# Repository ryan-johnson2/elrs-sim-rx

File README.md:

# ELRS Sim RX

An ExpressLRS receiver to USB gamepad adapter for FPV simulators, built on an RP2040. Plug it
in, bind your radio to it, and the radio shows up as a game controller in Liftoff,
Velocidrone, Uncrashed, Tryp and anything else that reads a standard HID gamepad. You fly the
sim over the same radio link, packet rate and radio setup you fly for real.

## How this was made

All of the code and all of the hardware design in this repository were produced with AI:
Anthropic's Claude, working through Claude Code. That covers the firmware, the configuration
page, the tests, the schematics and PCB layouts, the printed cases and the documentation.

A person directed the work, built the hardware, and tested it on the bench and in simulators.
Read it with that in mind: parts of it have had real use, parts have only passed automated
checks, and the status table below says which.

## Status

| Part | State |
|---|---|
| Firmware core: gamepad, CRSF, failsafe, receiver power, bind, model match, passthrough | In daily use on the perfboard prototype |
| Newer firmware features: profiles, the lite build, the onboard status LED, bootloader without the drive | Pass the automated tests; little or no time on hardware yet |
| Configuration page | In use; the four-tab layout, profiles and one-click update are tested against a simulated device only |
| Prototype hardware (breadboard, then perfboard) | Built and working |
| Carrier PCB v0.2 | Ordered, not yet received or tested |
| Integrated PCB with the RP2040 on board | Draft: placed, not routed |
| Printed cases | Designed and checked for overlaps in CAD; not confirmed on a printer |
| Hosting on GitHub Pages, release and development builds | CI builds, tests and publishes the development firmware; no release tagged yet |

## What it does

- **Gamepad:** 8 axes at 16-bit resolution, with the full 11-bit CRSF channel range kept, and
  36 buttons derived from switch channels. A report goes out on every CRSF frame, up to the
  1 kHz USB polling rate.
- **Failsafe:** sticks centred and throttle low within 100 ms of losing the link.
- **Receiver power:** a front-panel button switches the receiver off and on, so the dongle
  can stay plugged in while you fly something else. A long press puts the receiver into bind
  mode.
- **Status light:** the button's LED ring mirrors the receiver's own status LED patterns.
- **Profiles:** 16 named channel-to-axis and channel-to-button mappings stored on the dongle.
- **Receiver updates:** Betaflight-compatible passthrough, so the ExpressLRS Web Flasher or
  Configurator can update the receiver and set its bind phrase through the dongle.
- **Receiver settings:** model match, and on ExpressLRS 4.0 or newer the receiver's own
  settings, from the configuration page.
- **No drivers:** a standard USB gamepad plus a serial port on Windows, Linux and macOS.

## Hardware

There are three generations of the same circuit: a hand-built prototype, a carrier PCB that
takes an RP2040-Zero module, and a draft board with the RP2040 itself fitted.
**[docs/HARDWARE.md](docs/HARDWARE.md)** is the index, with the state of each.

| | Page |
|---|---|
| Parts list, pin plan, costs | [docs/HBOM.md](docs/HBOM.md) |
| Breadboard build, step by step | [web/guides/breadboard-build.html](web/guides/breadboard-build.html) |
| Perfboard layout, hole by hole | [web/guides/perfboard-layout.html](web/guides/perfboard-layout.html) |
| Carrier PCB v0.2 | [hardware/carrier/](hardware/carrier/README.md) |
| Integrated PCB draft | [hardware/board/](hardware/board/README.md) |
| Cases | [prototype](hardware/case-proto/README.md), [carrier](hardware/case-carrier/README.md) |
| Bring-up checklist | [docs/BRINGUP.md](docs/BRINGUP.md) |
| What the status light means | [docs/LED-BEHAVIOUR.md](docs/LED-BEHAVIOUR.md) |

The simplest build needs no PCB at all: an RP2040-Zero and a receiver joined by four wires
(5V, GND, GP0 to the receiver's RX pad, GP1 to its TX pad), running the lite firmware.

## Firmware

Pico SDK and TinyUSB, in C. One build tree produces two files:

| File | For |
|---|---|
| `elrs_sim_rx.uf2` | Any board with the power switch, button and LED ring |
| `elrs_sim_rx_lite.uf2` | A module wired straight to a receiver. The receiver is on whenever USB is |

To flash: hold BOOT while plugging the board in, then copy the file onto the `RPI-RP2` drive
that appears. After that, updates can be done from the configuration page.

Details, the console commands and the flash layout are in
[docs/FIRMWARE.md](docs/FIRMWARE.md).

## Configuring

`web/index.html` is a single static page that talks to the dongle over Web Serial, so it
needs Chrome or Edge on a desktop. Click Connect and pick the device. It has five tabs:

- **Controller** (the page it opens on): profiles and saving, live channels, the axis and
  button mapping, link status, receiver power, bind, model match and the receiver's own settings.
- **Firmware:** update the dongle itself.
- **RX flashing:** the short steps for updating the receiver's ExpressLRS firmware through
  the dongle, with a link to the ExpressLRS Web Flasher.
- **Console:** the raw console and counters.
- **Docs:** the user documentation.

Changes apply at once; **Save to device** writes them to the active profile.

The same serial port answers a plain terminal at any baud rate: type `help`.

See [docs/WEBUI.md](docs/WEBUI.md) for how the page works and is hosted, and
[docs/WINDOWS.md](docs/WINDOWS.md) for the one optional Windows driver step.

## Building

Everything runs in Docker; nothing else needs installing on the host.

```
tools/build.sh        # firmware -> firmware/build/elrs_sim_rx.uf2 and elrs_sim_rx_lite.uf2
tools/test.sh         # host unit tests for the hardware-independent core
tools/test-web.sh     # configuration page and bootloader tests (Playwright image)
tools/serve.sh        # serve the page and the latest firmware over HTTPS on the LAN
tools/flash.sh        # flash a board plugged into this machine (Linux)
tools/shell.sh        # shell inside the build container
```

`tools/serve.sh` is the easy way to work when the build machine and the PC with the dongle
are different computers: open the address it prints in Chrome or Edge on that PC.

Hardware builds (PCB generation and checks, order files, case exports) are listed in
[docs/HARDWARE.md](docs/HARDWARE.md).

## Versions

The firmware and the configuration page are released together under one version: a `vX.Y.Z`
tag on `main`. The page is published alongside the firmware it flashes, so the two always
match. Builds that are not on a release tag name themselves after the next patch version, the
number of commits since the last release and the commit, for example `0.1.1-dev.4+3664729`;
`tools/version.sh` works this out and `version` on the console reports it.

Each board has its own revision, printed on its silkscreen, and is not part of the release
number. The commit a board was ordered from is tagged `<board>-v<revision>`, for example
`carrier-v0.2`. Release notes say which boards a firmware release supports.

## Layout

| Path | Contents |
|------|----------|
| `firmware/` | Firmware. `core/` is hardware independent and unit tested; `src/` is the RP2040 side |
| `tests/` | Host unit tests, and browser tests for the configuration page |
| `web/` | The configuration page, the bootloader flasher, and the build guides |
| `hardware/` | KiCad projects for the two PCBs, their generator scripts, and the OpenSCAD cases |
| `docs/` | Hardware index, parts list, bring-up checklist, firmware and page notes |
| `tools/` | Build container and helper scripts |
| `.github/workflows/` | CI: build, test, and publishing of the page and firmware |

Only sources are committed. Firmware binaries, PCB renders and order files, case STLs and the
wiring PDF are generated by the commands above.

## License

Firmware and documentation are licensed under the Apache License 2.0. See `LICENSE`.

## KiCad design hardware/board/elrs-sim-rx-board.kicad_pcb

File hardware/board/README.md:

# Integrated board (draft v0.1, placed, not routed)

KiCad 9 project for the next board after the carrier: the RP2040 itself is on the board, so
there is no module to solder. The fab fits everything except the receiver and the button leads.

| | |
|---|---|
| Board | 22 x 39.1 mm, 2 layers, same outline, receiver cut-out, button pads and M2 hole as carrier v0.2 |
| MCU | RP2040, W25Q16 flash, 12 MHz crystal, XC6206 3.3 V regulator, USB-C socket |
| Kept from the module | BOOT button. No RESET button; the RUN pin has a pull-up |
| Status light | One plain LED on GP25. The firmware drives GP25 and the RP2040-Zero's RGB LED on GP16 with the same pattern, so one build serves both boards |
| Receiver | Happymodel EP2 soldered by its castellated edge over the cut-out, as on the carrier |
| Button | Four pads: LED+, LED-, BTN, BTN. Leave the button off for the no-button version |
| Circuit | Otherwise the carrier's: TPS22918 load switch on GP2, 2N7002 LED driver on GP4, button on GP3, CRSF on GP0 / GP1 |
| Debug | SWCLK and SWDIO test pads |

## State

- Schematic: complete, ERC clean. It is drawn label-style (every pin carries a net name, no
  wires) because it is generated from a parts table in `gen/gen_sch.py`.
- Placement: all 48 footprints placed, no courtyard overlaps.
- Routing: none yet. `gen/route.sh` runs the Freerouting autorouter on the exported
  `out/elrs-sim-rx-board.dsn` and imports the result; it has not been run.
- Part numbers: only the RP2040, USB-C socket, regulator, load switch and LED driver have LCSC
  numbers. The flash, crystal, button, LED and all the 0402 passives still need choosing, and
  the crystal's load capacitors (drawn as 15 pF) depend on the crystal picked.

## To do before this can be ordered

1. Route it, then review the result by hand: USB pair, crystal, decoupling and the ground pour.
2. Choose and confirm every part number; pick the crystal and set C17 / C18 to match.
3. Decide on USB ESD protection (none drawn).
4. Check the EP2 pad pitch (shared with the carrier; `RX_PITCH` in `gen/gen_pcb.py`).
5. Firmware: confirm the build boots with this flash and crystal. The pin map is unchanged.

## Regenerate and check

```
tools/kicad.sh hardware/board/gen/build.sh          # schematic, placement, ERC, DRC, renders
hardware/board/gen/route.sh                          # autoroute and import (run on the host)
```

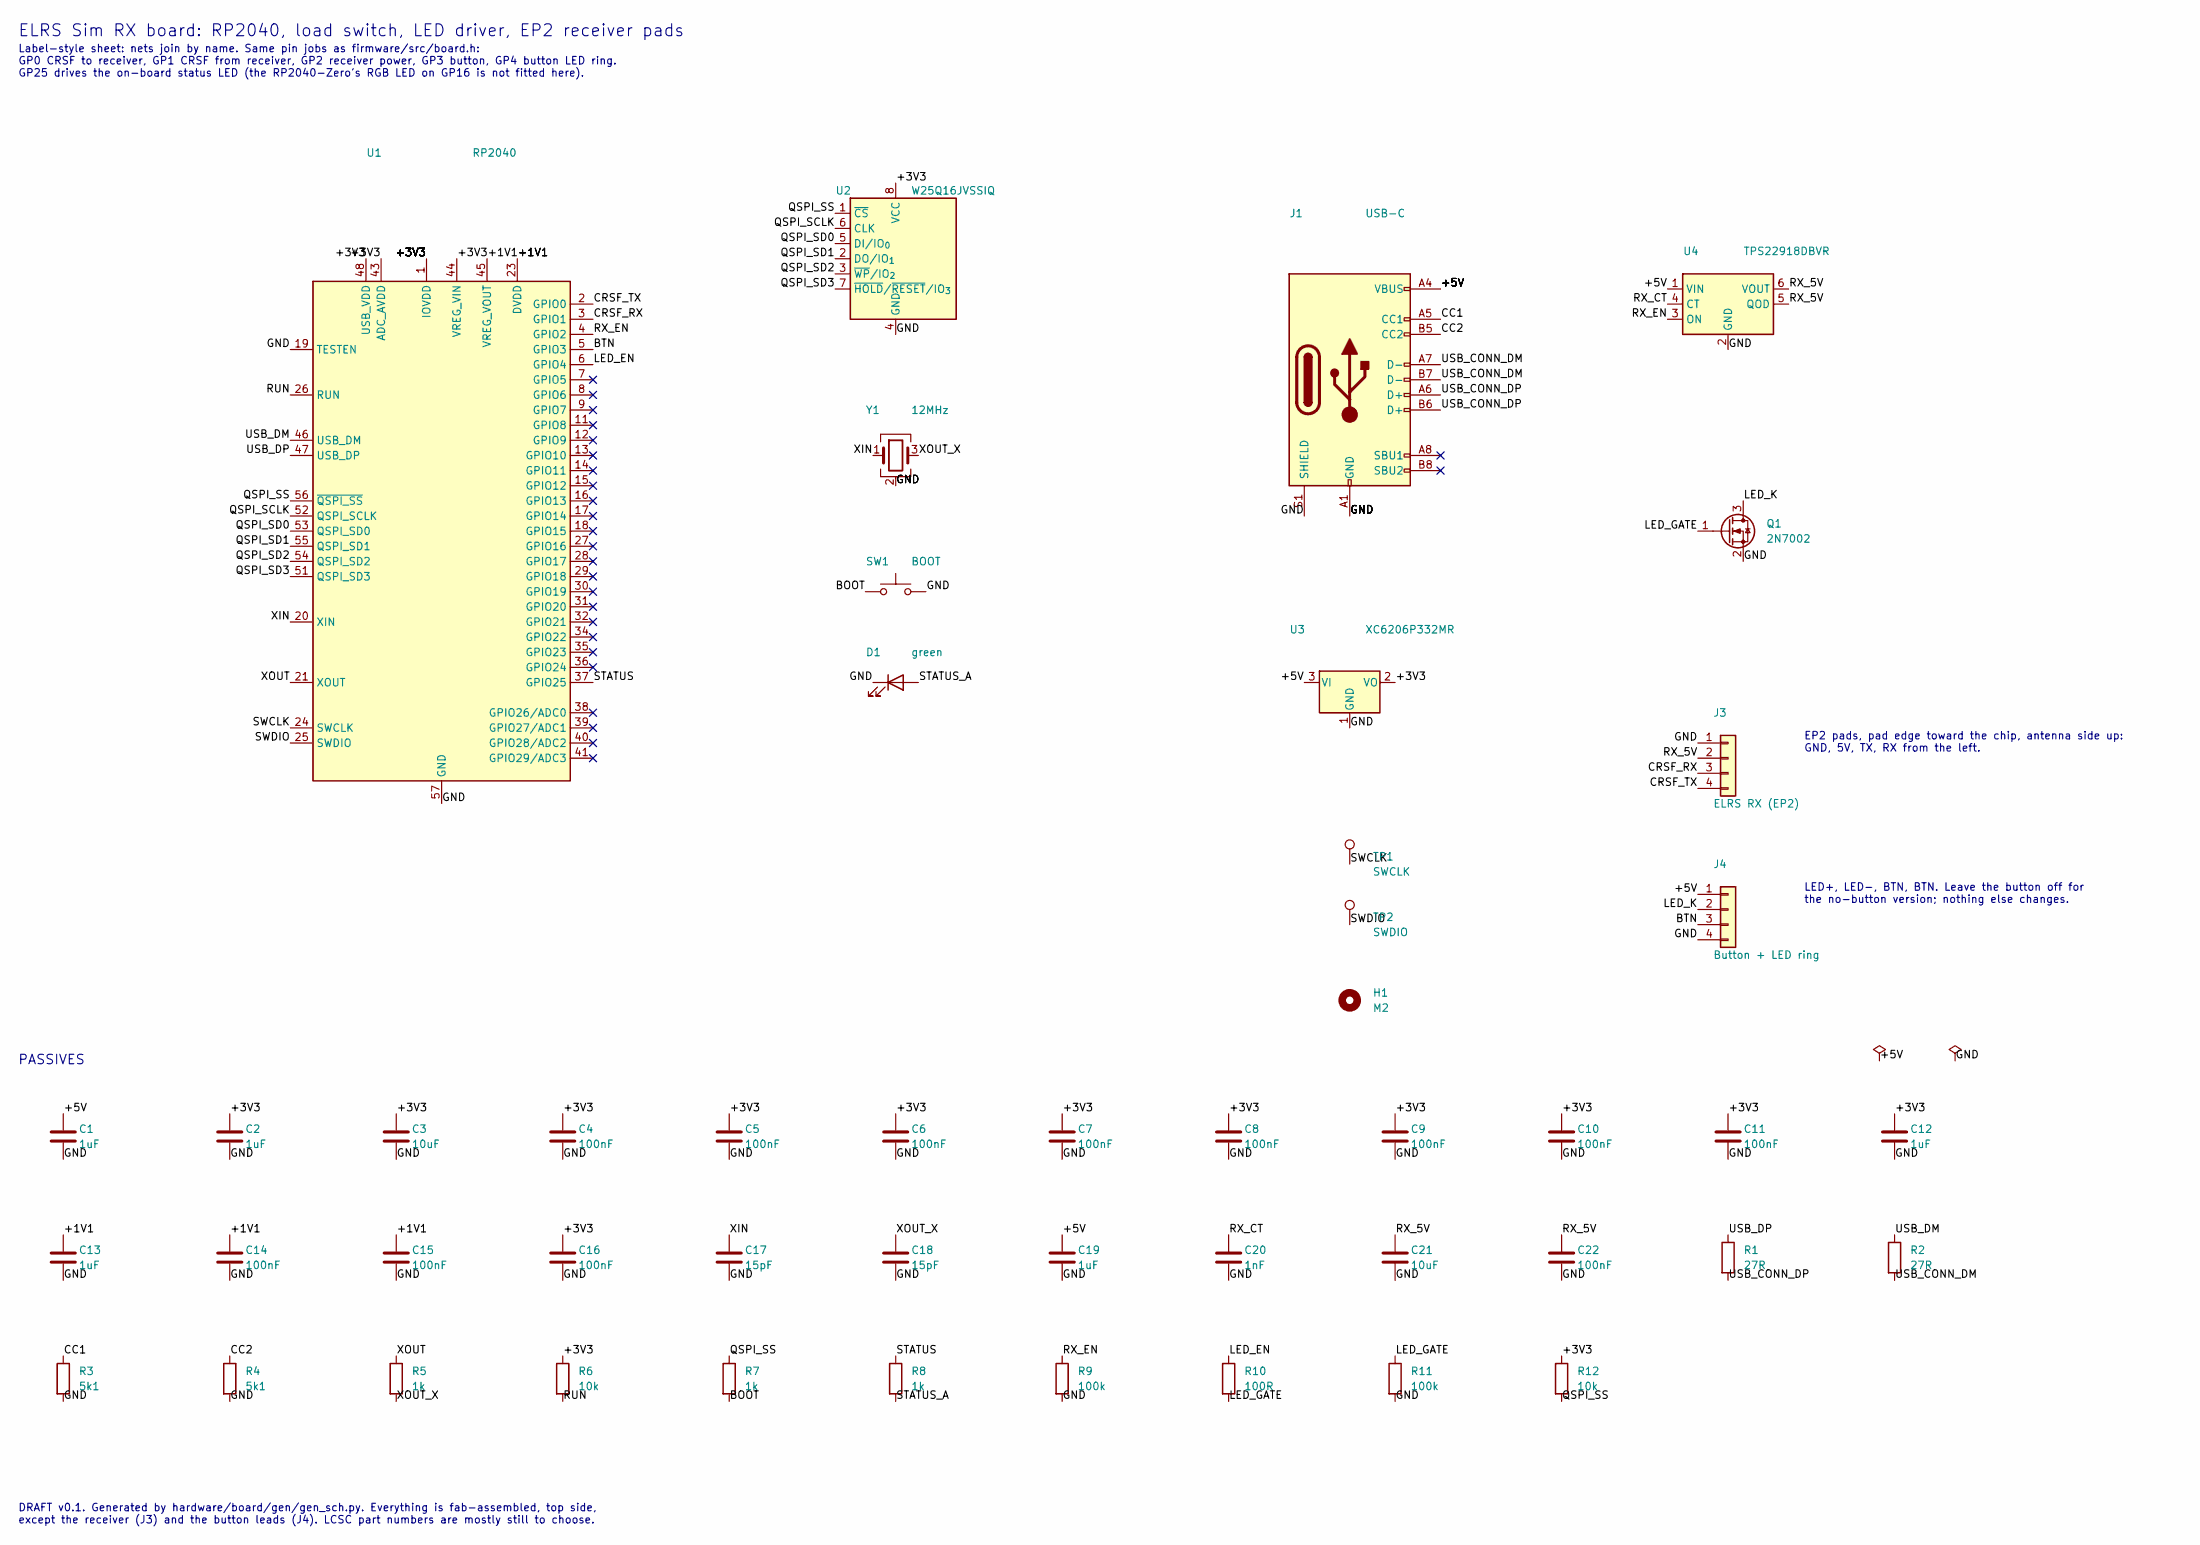
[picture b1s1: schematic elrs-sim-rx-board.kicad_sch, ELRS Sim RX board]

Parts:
C1, C2, C12, C13, C19: 1uF; C_0402_1005Metric
C3: 10uF; C_0603_1608Metric
C4, C5, C6, C7, C8, C9, C10, C11, C14, C15, C16, C22: 100nF; C_0402_1005Metric
C17, C18: 15pF; C_0402_1005Metric
C20: 1nF; C_0402_1005Metric
C21: 10uF; C_0805_2012Metric
D1: green; LED_0603_1608Metric
H1: M2; MountingHole_2.2mm_M2
J1: USB-C; USB_C_Receptacle_HRO_TYPE-C-31-M-12; MPN TYPE-C-31-M-12; LCSC C165948
J3: ELRS RX (EP2); ELRS_RX_4pad_castellated
J4: Button + LED ring; PinHeader_1x04_P2.54mm_Vertical
Q1: 2N7002; SOT-23; LCSC C8545
R1, R2: 27R; R_0402_1005Metric
R3, R4: 5k1; R_0402_1005Metric
R5, R7, R8: 1k; R_0402_1005Metric
R6, R12: 10k; R_0402_1005Metric
R9, R11: 100k; R_0402_1005Metric
R10: 100R; R_0402_1005Metric
SW1: BOOT; SW_SPST_B3U-1000P
TP1: SWCLK; TestPoint_Pad_D1.0mm
TP2: SWDIO; TestPoint_Pad_D1.0mm
U1: RP2040; QFN-56-1EP_7x7mm_P0.4mm_EP3.2x3.2mm; MPN RP2040; LCSC C2040
U2: W25Q16JVSSIQ; SOIC-8_5.3x5.3mm_P1.27mm; MPN W25Q16JVSSIQ
U3: XC6206P332MR; SOT-23; MPN XC6206P332MR; LCSC C5446
U4: TPS22918DBVR; SOT-23-6; MPN TPS22918DBVR; LCSC C131941
Y1: 12MHz; Crystal_SMD_3225-4Pin_3.2x2.5mm

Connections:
/+1V1: C13.1, C14.1, C15.1, U1.23 (DVDD), U1.45 (VREG_VOUT), U1.50 (DVDD)
/+3V3: C2.1, C3.1, C4.1, C5.1, C6.1, C7.1, C8.1, C9.1, C10.1, C11.1, C12.1, C16.1, R6.1, R12.1, U1.1 (IOVDD), U1.10 (IOVDD), U1.22 (IOVDD), U1.33 (IOVDD), U1.42 (IOVDD), U1.43 (ADC_AVDD), U1.44 (VREG_VIN), U1.48 (USB_VDD), U1.49 (IOVDD), U2.8 (VCC), U3.2 (VO)
/+5V: C1.1, C19.1, J1.A4 (VBUS), J1.A9 (VBUS), J1.B4 (VBUS), J1.B9 (VBUS), J4.1, U3.3 (VI), U4.1 (VIN)
/BOOT: R7.2, SW1.1
/BTN: J4.3, U1.5 (GPIO3)
/CC1: J1.A5 (CC1), R3.1
/CC2: J1.B5 (CC2), R4.1
/CRSF_RX: J3.3, U1.3 (GPIO1)
/CRSF_TX: J3.4, U1.2 (GPIO0)
/GND: C1.2, C2.2, C3.2, C4.2, C5.2, C6.2, C7.2, C8.2, C9.2, C10.2, C11.2, C12.2, C13.2, C14.2, C15.2, C16.2, C17.2, C18.2, C19.2, C20.2, C21.2, C22.2, D1.1 (K), J1.A1 (GND), J1.A12 (GND), J1.B1 (GND), J1.B12 (GND), J1.S1 (SHIELD), J3.1, J4.4, Q1.2 (S), R3.2, R4.2, R9.2, R11.2, SW1.2, U1.19 (TESTEN), U1.57 (GND), U2.4 (GND), U3.1 (GND), U4.2 (GND), Y1.2 (G), Y1.4 (G)
/LED_EN: R10.1, U1.6 (GPIO4)
/LED_GATE: Q1.1 (G), R10.2, R11.1
/LED_K: J4.2, Q1.3 (D)
/QSPI_SCLK: U1.52 (QSPI_SCLK), U2.6 (CLK)
/QSPI_SD0: U1.53 (QSPI_SD0), U2.5 (DI/IO_{0})
/QSPI_SD1: U1.55 (QSPI_SD1), U2.2 (DO/IO_{1})
/QSPI_SD2: U1.54 (QSPI_SD2), U2.3 (~WP/IO_{2})
/QSPI_SD3: U1.51 (QSPI_SD3), U2.7 (~HOLD/~RESET/IO_{3})
/QSPI_SS: R7.1, R12.2, U1.56 (~QSPI_SS), U2.1 (~CS)
/RUN: R6.2, U1.26 (RUN)
/RX_5V: C21.1, C22.1, J3.2, U4.5 (QOD), U4.6 (VOUT)
/RX_CT: C20.1, U4.4 (CT)
/RX_EN: R9.1, U1.4 (GPIO2), U4.3 (ON)
/STATUS: R8.1, U1.37 (GPIO25)
/STATUS_A: D1.2 (A), R8.2
/SWCLK: TP1.1, U1.24 (SWCLK)
/SWDIO: TP2.1, U1.25 (SWDIO)
/USB_CONN_DM: J1.A7 (D-), J1.B7 (D-), R2.2
/USB_CONN_DP: J1.A6 (D+), J1.B6 (D+), R1.2
/USB_DM: R2.1, U1.46 (USB_DM)
/USB_DP: R1.1, U1.47 (USB_DP)
/XIN: C17.1, U1.20 (XIN), Y1.1
/XOUT: R5.1, U1.21 (XOUT)
/XOUT_X: C18.1, R5.2, Y1.3

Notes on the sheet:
ELRS Sim RX board: RP2040, load switch, LED driver, EP2 receiver pads
Label-style sheet: nets join by name. Same pin jobs as firmware/src/board.h: GP0 CRSF to receiver, GP1 CRSF from receiver, GP2 receiver power, GP3 button, GP4 button LED ring. GP25 drives the on-board status LED (the RP2040-Zero's RGB LED on GP16 is not fitted here).
EP2 pads, pad edge toward the chip, antenna side up: GND, 5V, TX, RX from the left.
LED+, LED-, BTN, BTN. Leave the button off for the no-button version; nothing else changes.
PASSIVES
DRAFT v0.1. Generated by hardware/board/gen/gen_sch.py. Everything is fab-assembled, top side, except the receiver (J3) and the button leads (J4). LCSC part numbers are mostly still to choose.

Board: 2 copper layers, 48 parts (0 on the bottom side), 34 nets, no tracks yet.

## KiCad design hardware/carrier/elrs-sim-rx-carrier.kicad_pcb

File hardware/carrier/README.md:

# Carrier board (draft v0.2)

KiCad 9 project for the Phase 2 carrier in [docs/HBOM.md](../../docs/HBOM.md). v0.2 follows the
Phase 1 breadboard and perfboard builds: the module is soldered in directly, the back-row
socket is gone, and the receiver mount was redrawn for the Happymodel EP2. Five boards were made
(JLCPCB, ordered 2026-11-14); the first was assembled and brought up on 2026-11-24.

| | |
|---|---|
| Board | 22 x 39.1 mm with the lower left corner cut away for the receiver, 2 layers, one M2 hole |
| MCU | RP2040-Zero soldered in by its own pin headers: two 1x9 rows of plated holes (J1, J2) and five unconnected holes for the back-row pins (J5), so the module drops in unmodified |
| Receiver | Happymodel EP2, antenna side up, soldered by its castellated edge onto four SMD pads (J3) and hanging over the cut-out, since it has parts on both faces |
| Button | Four pads (J4) marked by function: LED+, LED-, BTN, BTN. The switch's two leads go to the two BTN pads, either way round (one of them is ground) |
| Fab-assembled | U1, Q1, R1 to R3, C1 to C4. All top side, all under the module |
| Hand-soldered | The module, the receiver, the button leads |

## Circuit

Electrically the same as the Phase 1 breadboard build with the planned Phase 2 swaps:

- TPS22918 load switch replaces AO3401A + 2N7000 + 10 k. GP2 drives ON directly; R1 (100 k)
  holds the receiver off until firmware takes over. QOD is tied to VOUT so the rail collapses
  quickly, which the power-cycle bind sequence needs.
- 2N7002 replaces the 2N7000 LED ring driver, same 100 R gate resistor and 100 k pull-down.
- Pin map is unchanged from `firmware/src/board.h`. No firmware changes are needed.

## Checks

1. **EP2 pad order: confirmed on board 1** (2026-11-24: receiver powers, CRSF frames arrive on
   GP1, passthrough flashing works). GND, 5V, TX, RX from the left with the pad edge toward the
   module and the antenna side up; ground is the end pad on the antenna's side. The EP2 itself
   has no pad labels.
2. **EP2 pad pitch and underside: checked.** A photo of a real EP2 on a steel rule
   (2026-11-14) shows the outer pads 7.6 mm apart, so 2.54 mm pitch, centred on the edge, and
   nothing taller than a bare pad within 2.2 mm of the pad edge on the ESP side.
3. **RP2040-Zero pin grid.** Two rows of nine, 15.24 mm apart, pin 1 (5V left, GP0 right) at
   the USB end, and the five back-row holes in line with the last pin of each side row.
   Confirmed on board 1: an unmodified module drops in.
4. **Height under the module.** The SMD parts sit under the soldered-in module, which stands
   about 2.5 mm off the board on its header spacers. The tallest part is the 0805 capacitor.
5. **LCSC part numbers** in the schematic `LCSC` field were filled in from memory. Confirm
   each one, and add one for U1, before generating a JLCPCB BOM.
6. **Mounting.** One M2 hole on the arm beside the receiver. The receiver is held only by
   its four solder joints, so the case should support its free end.

## Files

- `elrs-sim-rx-carrier.kicad_pro`, `.kicad_sch`, `.kicad_pcb`: the project.
- `carrier.kicad_sym`, `sym-lib-table`: project symbol library (TPS22918).
- `carrier.pretty/`, `fp-lib-table`: project footprint library (receiver landing).
- `gen/`: the scripts that produced the draft. Placement and routing are written out by hand
  in `gen_pcb.py`. Regenerating overwrites the schematic and board, so stop using the scripts
  once you start editing in KiCad.

## Regenerate and check

KiCad runs in the official container; nothing is installed on the host.

```
tools/kicad.sh hardware/carrier/gen/build.sh          # regenerate, ERC, DRC, previews
tools/kicad.sh hardware/carrier/gen/build.sh check    # ERC, DRC, previews only
```

Outputs land in `out/` (gitignored): `schematic.pdf`, `render-top.png`, `render-bottom.png`,
`layout-top.svg`, `layout-bottom.svg`, `erc.rpt`, `drc.rpt`.

ERC is clean. DRC reports three `lib_footprint_mismatch` warnings for J1, J2 and J5, which are
expected: their courtyards are trimmed where the three rows of holes meet, and J5 has no
silkscreen. The v0.1 files are kept in `out/v0.1-backup/`.

`tools/kicad.sh hardware/carrier/gen/fab.sh` writes the JLCPCB order files to `out/fab/`:
`gerbers.zip`, `bom.csv` and `cpl.csv`. Only the fab-assembled parts are listed.

After opening the board in the KiCad GUI, press B once to refill zones.

## Bring-up notes

Board 1 at first received nothing from the receiver and could not flash it by passthrough. The
cause was a dry joint on the module's GP1 header pin, not the receiver's castellations. The
serial lines idle at 3.3 V whether they are connected, swapped or open, so a meter on the
powered board does not show this; use continuity from the top of each receiver castellation to
the module pin, or the firmware's `rxprobe` command (see docs/FIRMWARE.md).

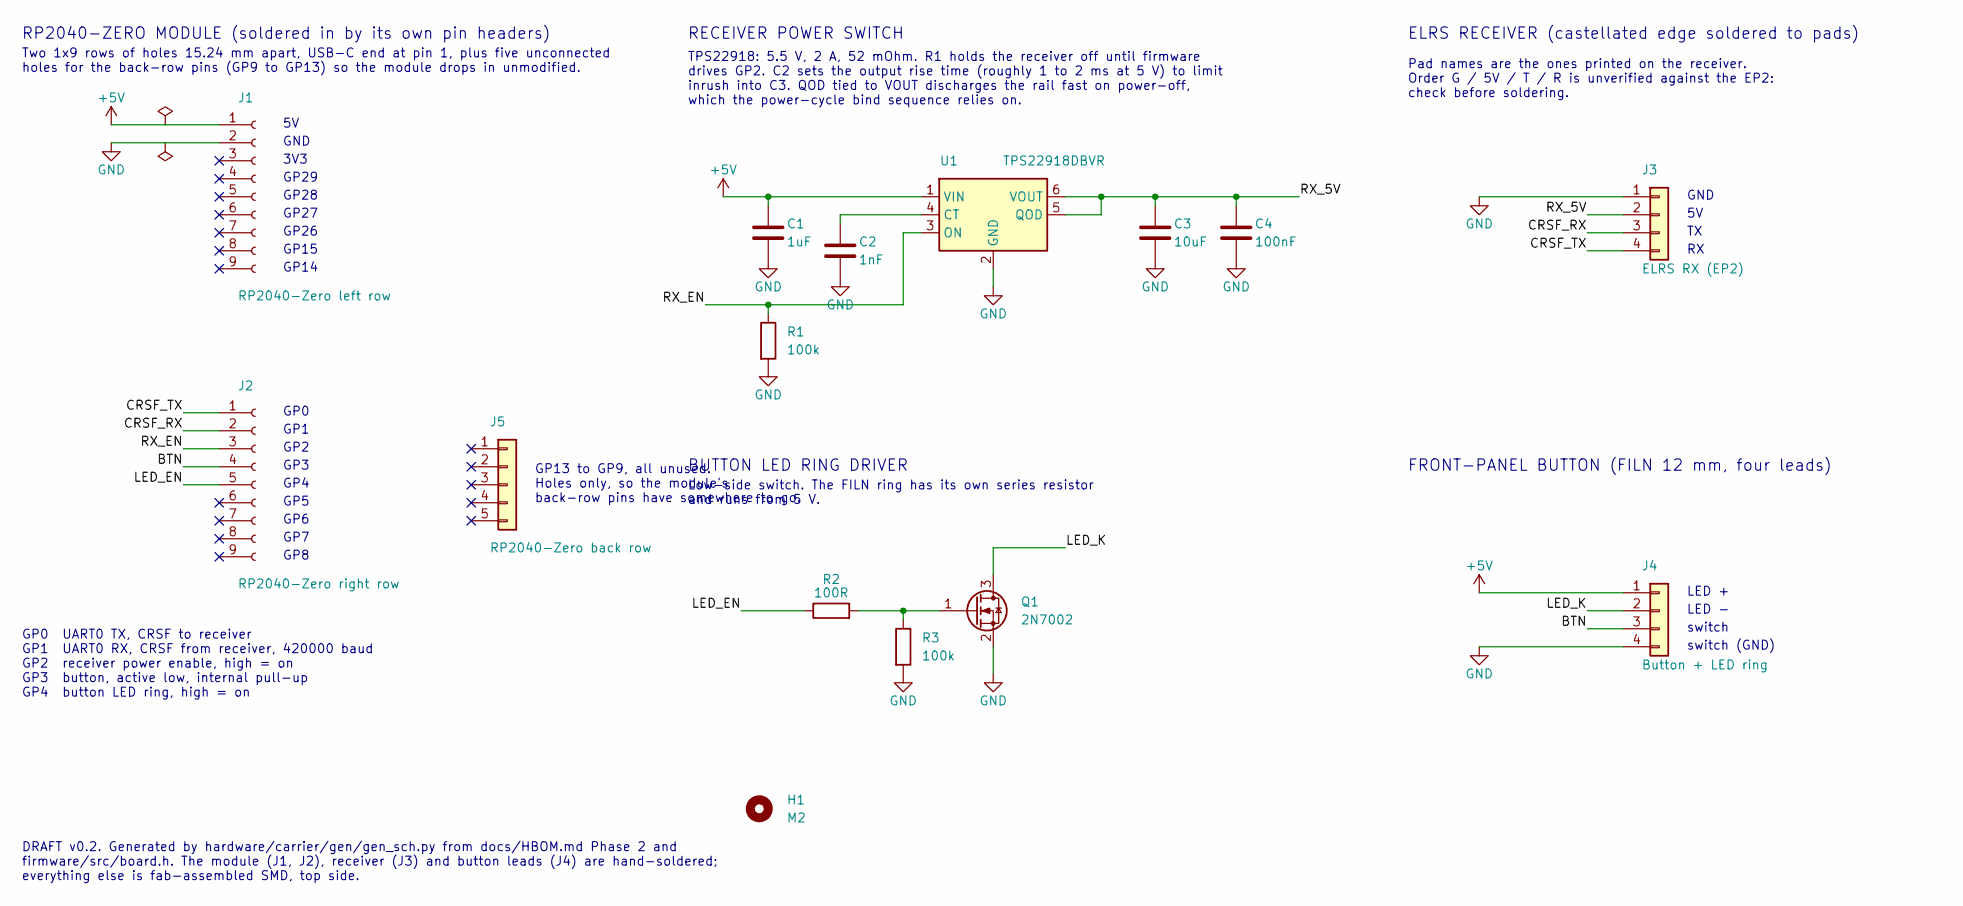
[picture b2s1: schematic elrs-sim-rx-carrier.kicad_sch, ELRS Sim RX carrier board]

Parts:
C1: 1uF; C_0603_1608Metric; LCSC C15849
C2: 1nF; C_0603_1608Metric; LCSC C1588
C3: 10uF; C_0805_2012Metric; LCSC C15850
C4: 100nF; C_0603_1608Metric; LCSC C14663
H1: M2; MountingHole_2.2mm_M2
J1: RP2040-Zero left row; PinHeader_1x09_P2.54mm_Vertical
J2: RP2040-Zero right row; PinHeader_1x09_P2.54mm_Vertical
J3: ELRS RX (EP2); ELRS_RX_4pad_castellated
J4: Button + LED ring; PinHeader_1x04_P2.54mm_Vertical
J5: RP2040-Zero back row; PinHeader_1x05_P2.54mm_Vertical
Q1: 2N7002; SOT-23; LCSC C8545
R1, R3: 100k; R_0603_1608Metric; LCSC C25803
R2: 100R; R_0603_1608Metric; LCSC C22775
U1: TPS22918DBVR; SOT-23-6; MPN TPS22918DBVR; LCSC C131941

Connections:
+5V: C1.1, J1.1, J4.1, U1.1 (VIN)
/BTN: J2.4, J4.3
/CRSF_RX: J2.2, J3.3
/CRSF_TX: J2.1, J3.4
/LED_EN: J2.5, R2.1
/LED_K: J4.2, Q1.3 (D)
/RX_5V: C3.1, C4.1, J3.2, U1.5 (QOD), U1.6 (VOUT)
/RX_EN: J2.3, R1.1, U1.3 (ON)
GND: C1.2, C2.2, C3.2, C4.2, J1.2, J3.1, J4.4, Q1.2 (S), R1.2, R3.2, U1.2 (GND)
unnamed: Q1.1 (G), R2.2, R3.1
unnamed: C2.1, U1.4 (CT)

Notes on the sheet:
RP2040-ZERO MODULE (soldered in by its own pin headers)
Two 1x9 rows of holes 15.24 mm apart, USB-C end at pin 1, plus five unconnected holes for the back-row pins (GP9 to GP13) so the module drops in unmodified.
GND
3V3
GP29
GP28
GP27
GP26
GP15
GP14
GP0
GP1
GP2
GP3
GP4
GP5
GP6
GP7
GP8
GP13 to GP9, all unused. Holes only, so the module's back-row pins have somewhere to go.
GP0 UART0 TX, CRSF to receiver GP1 UART0 RX, CRSF from receiver, 420000 baud GP2 receiver power enable, high = on GP3 button, active low, internal pull-up GP4 button LED ring, high = on
RECEIVER POWER SWITCH
TPS22918: 5.5 V, 2 A, 52 mOhm. R1 holds the receiver off until firmware drives GP2. C2 sets the output rise time (roughly 1 to 2 ms at 5 V) to limit inrush into C3. QOD tied to VOUT discharges the rail fast on power-off, which the power-cycle bind sequence relies on.
ELRS RECEIVER (castellated edge soldered to pads)
Pad names are the ones printed on the receiver. Order G / 5V / T / R is unverified against the EP2: check before soldering.
BUTTON LED RING DRIVER
Low-side switch. The FILN ring has its own series resistor and runs from 5 V.
FRONT-PANEL BUTTON (FILN 12 mm, four leads)
LED +
LED -
switch
switch (GND)
DRAFT v0.2. Generated by hardware/carrier/gen/gen_sch.py from docs/HBOM.md Phase 2 and firmware/src/board.h. The module (J1, J2), receiver (J3) and button leads (J4) are hand-soldered; everything else is fab-assembled SMD, top side.

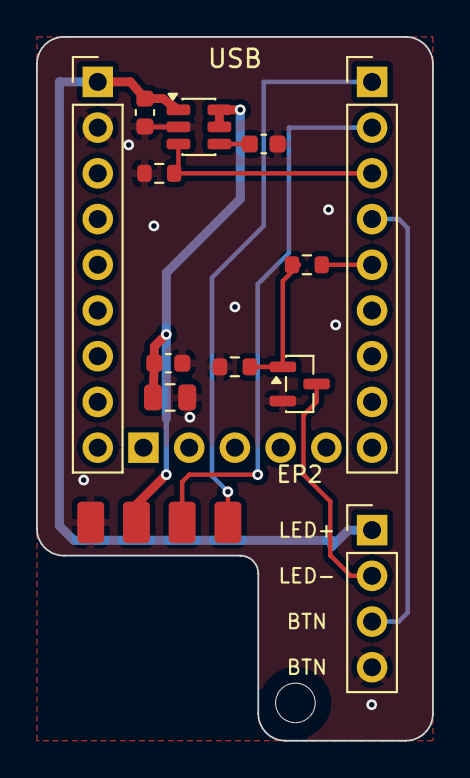
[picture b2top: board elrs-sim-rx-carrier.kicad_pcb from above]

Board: 2 copper layers, 22.0 x 39.1 mm, 15 parts (0 on the bottom side), 11 nets.

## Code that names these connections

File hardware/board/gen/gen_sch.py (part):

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gp.update({"GPIO26/ADC0": None, "GPIO27/ADC1": None, "GPIO28/ADC2": None, "GPIO29/ADC3": None})
for k in ("GPIO26", "GPIO27", "GPIO28", "GPIO29"):
    del gp[k]
gp.update({"GPIO0": "CRSF_TX", "GPIO1": "CRSF_RX", "GPIO2": "RX_EN", "GPIO3": "BTN", "GPIO4": "LED_EN",
           "GPIO25": "STATUS"})
part("MCU_RaspberryPi:RP2040", "U1", "RP2040", 70, 80, dict(gp, **{
    "IOVDD": "+3V3", "DVDD": "+1V1", "VREG_VIN": "+3V3", "VREG_VOUT": "+1V1", "USB_VDD": "+3V3",
    "ADC_AVDD": "+3V3", "GND": "GND", "TESTEN": "GND",
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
